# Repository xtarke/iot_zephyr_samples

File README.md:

# Zephyr RTOS Examples for Raspberry Pi Pico W

This repository contains a collection of IoT examples and utilities built with [Zephyr RTOS](https://zephyrproject.org/) specifically targeted for the Raspberry Pi Pico W. It provides starting points for Wi-Fi connectivity, basic GPIO manipulation, and debugging configurations.

## Repository Structure

| Sample / Folder | Description |
| :--- | :--- |
| **`blinky`** | The classic "Hello World" of embedded systems. Toggles the onboard LED to verify the basic build system and GPIO functionality. |
| **`_debugger`** | Documentation and configuration files for debugging the RP2040. Includes a comprehensive guide for using the **Black Magic Probe**. |
| **`wifi_scan`** | Demonstrates how to initialize the Wi-Fi interface and perform an active scan to discover nearby wireless networks. |
| **`wifi_shell`** | Integrates the Zephyr shell subsystem, allowing you to interactively manage and monitor Wi-Fi connections via a serial terminal. |
| **`wifi_static`** | A template for establishing a Wi-Fi connection using a hardcoded/static network configuration (SSID and password). |

---

## Prerequisites

Before building these examples, ensure you have the standard (tested with v4.4.0) Zephyr development environment set up:

1. **Zephyr SDK:** Installed and configured on your host machine.
2. **West Tool:** The Zephyr meta-tool installed via Python pip.
3. **Pico W Board:** A Raspberry Pi Pico W and a suitable micro-USB cable.

*For detailed setup instructions, refer to the [official Zephyr Getting Started Guide](https://docs.zephyrproject.org/latest/develop/getting_started/index.html).*

---

## Building and Flashing

To build any of the samples in this repository, navigate to the specific sample's directory or specify it in your `west build` command. 

### 1. Build the Sample
Use `west` to build the firmware for the Raspberry Pi Pico W. For example, to build the `blinky` sample:

```bash
west build -b rpi_pico/rp2040/w -p blinky

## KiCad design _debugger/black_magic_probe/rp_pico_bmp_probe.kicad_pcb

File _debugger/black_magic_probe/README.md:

# Black Magic Probe (BMP) Hardware Adapter

This documentation describes the hardware schematic for configuring an STM32 BlackPill as a Black Magic Probe (BMP) debugger. This design breaks out the essential debug and serial interfaces necessary for flashing and interacting with embedded targets.

## Schematic Overview

The schematic details the pin routing from the BlackPill's microcontroller to dedicated external connectors, providing a unified interface for hardware debugging.

### Exposed Debug & Serial Interfaces

The following critical signals are exposed for target interaction:
*   **Serial Wire Debug (SWD):** `SWDIO` and `SWCLK`.
*   **JTAG Interface:** `TDI` and `TDO`.
*   **UART Bridge:** `TX` and `RX` lines for target serial communication.
*   **Control & Power:** Target reset (`RST`), `+3.3V`, and `GND`.

### Hardware Connectors
The design organizes these signals into specific pin headers for modular target connections:
*   **J1:** Groups a 3-pin interface, likely designated for the UART bridge or basic target control.
*   **J2:** The primary 4-pin debug header, exposing the SWD/JTAG signaling lines.
*   **Auxiliary Connectors:** Multiple 2-pin connectors utilized for power delivery (`+3.3V`, `GND`) and other localized signal pairs.

### Status Indicators

The schematic includes visual indicators to monitor the probe's state during execution:
*   **D1 (Status LED):**  Pin `PC14`, typically used for general error or operational status indication
.
*   **D2 (UART LED):** Providesvisual feedback for serial bridge activity (TX/RX traffic).

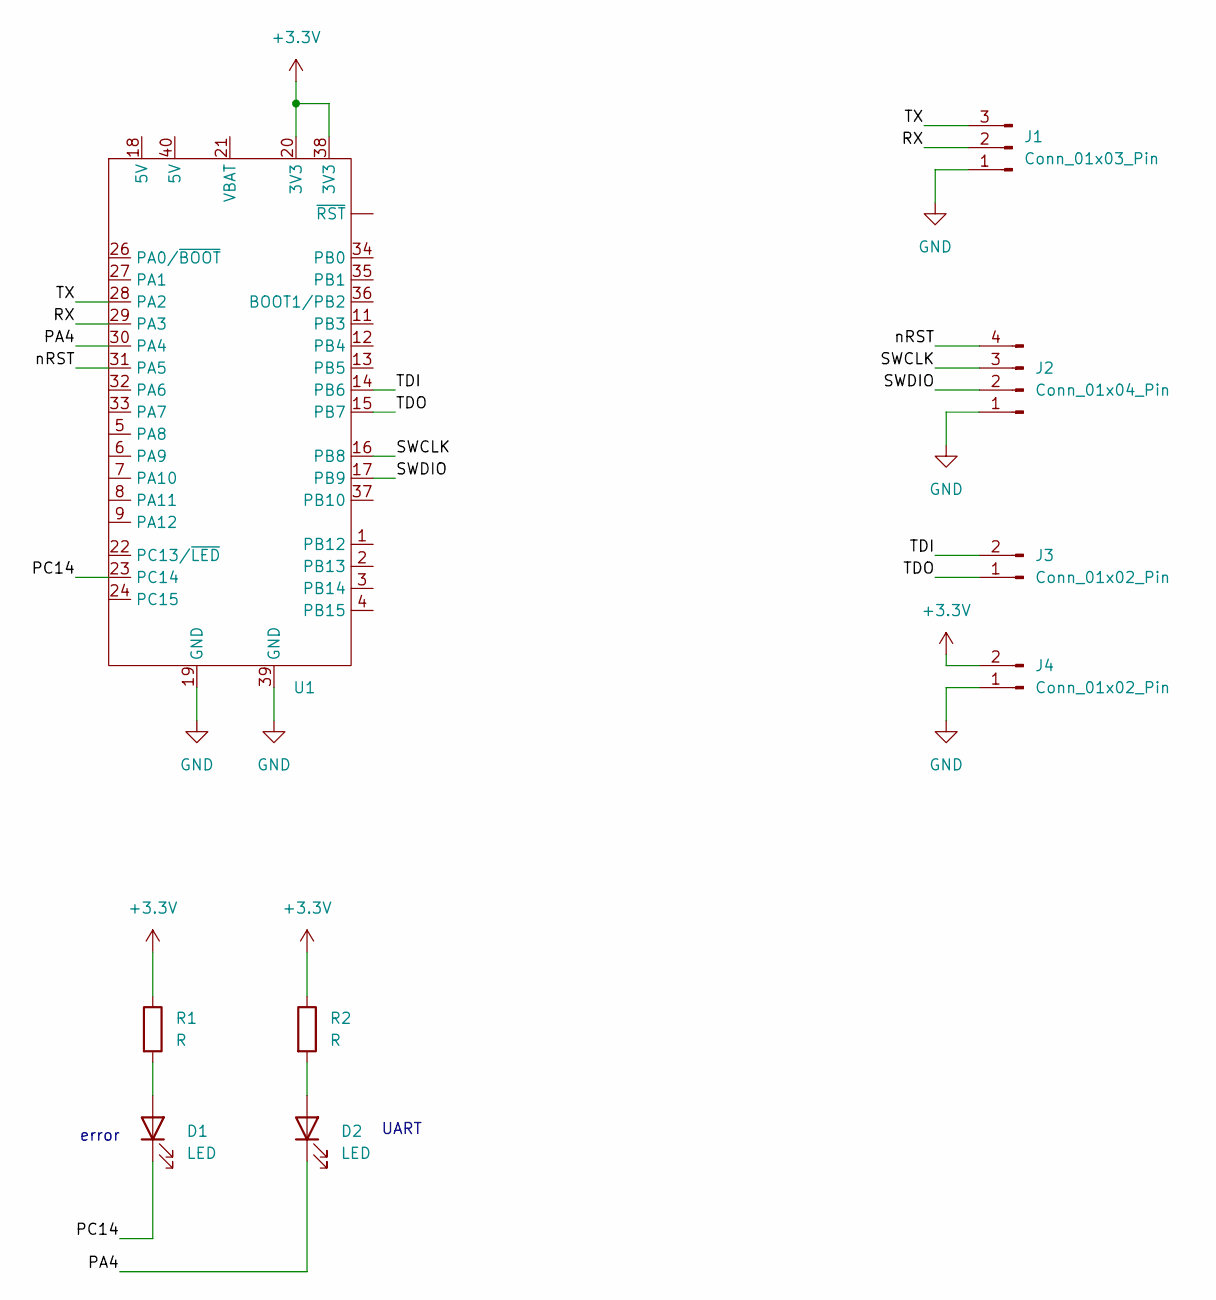
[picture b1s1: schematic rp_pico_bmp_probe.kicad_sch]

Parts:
D1, D2: LED; LED_D5.0mm
J1: Conn_01x03_Pin; Molex_KK-254_AE-6410-03A_1x03_P2.54mm_Vertical
J2: Conn_01x04_Pin; Molex_KK-254_AE-6410-04A_1x04_P2.54mm_Vertical
J3, J4: Conn_01x02_Pin; Molex_KK-254_AE-6410-02A_1x02_P2.54mm_Vertical
R1, R2: R; R_0805_2012Metric_Pad1.20x1.40mm_HandSolder
U1: Z_module_black_pill_STM32F411

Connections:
+3.3V: J4.2, R1.1, R2.1, U1.20 (3V3), U1.38 (3V3)
/PA4: D2.1 (K), U1.30 (PA4)
/PC14: D1.1 (K), U1.23 (PC14)
/RX: J1.2, U1.29 (PA3)
/SWCLK: J2.3, U1.16 (PB8)
/SWDIO: J2.2, U1.17 (PB9)
/TDI: J3.2, U1.14 (PB6)
/TDO: J3.1, U1.15 (PB7)
/TX: J1.3, U1.28 (PA2)
/nRST: J2.4, U1.31 (PA5)
GND: J1.1, J2.1, J4.1, U1.19 (GND), U1.39 (GND)
unnamed: D1.2 (A), R1.2
unnamed: D2.2 (A), R2.2

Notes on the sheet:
UART
error

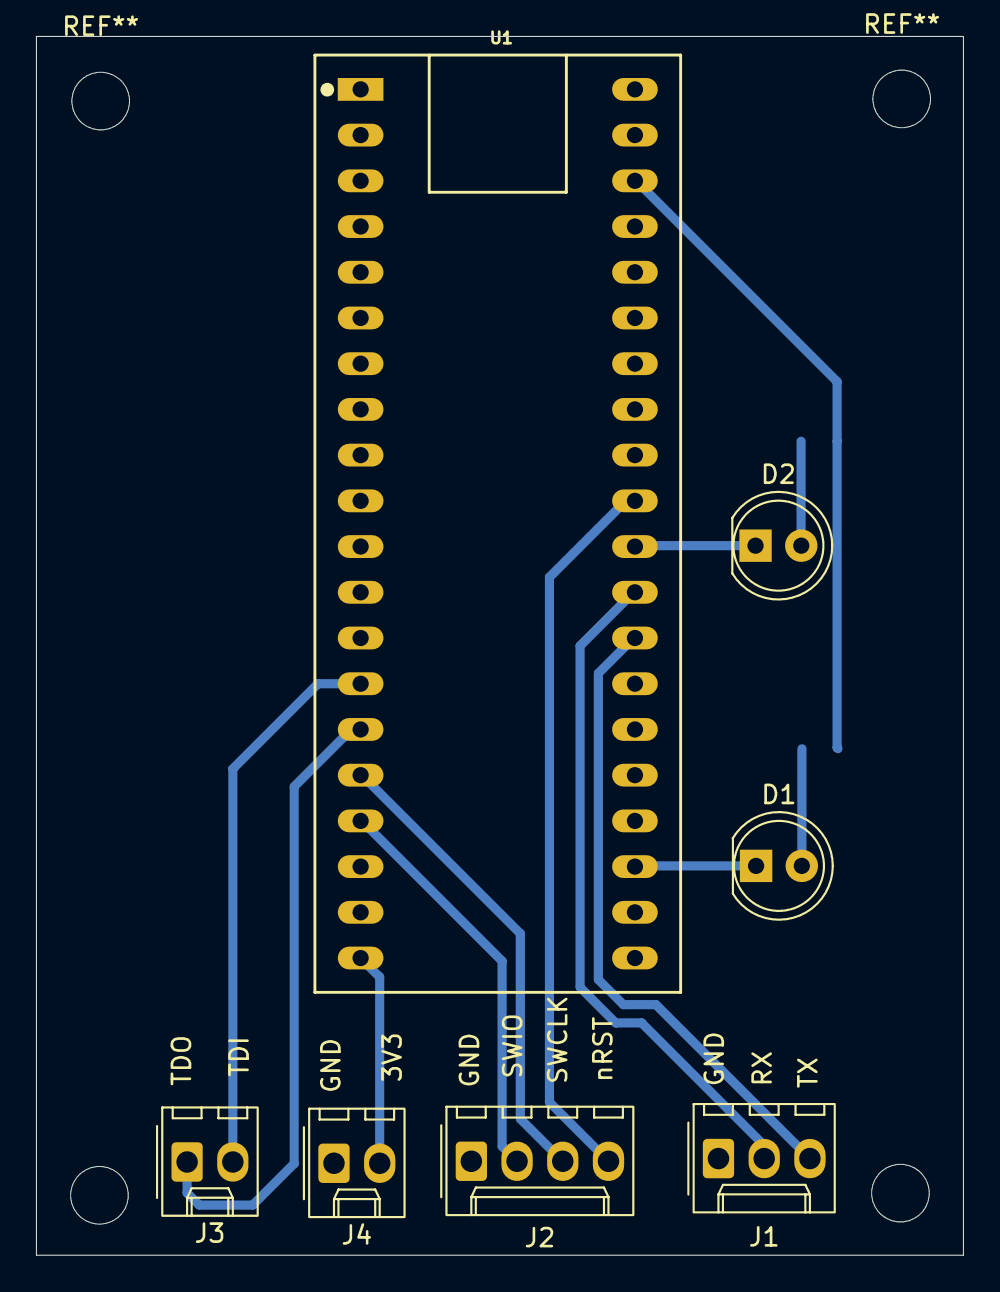
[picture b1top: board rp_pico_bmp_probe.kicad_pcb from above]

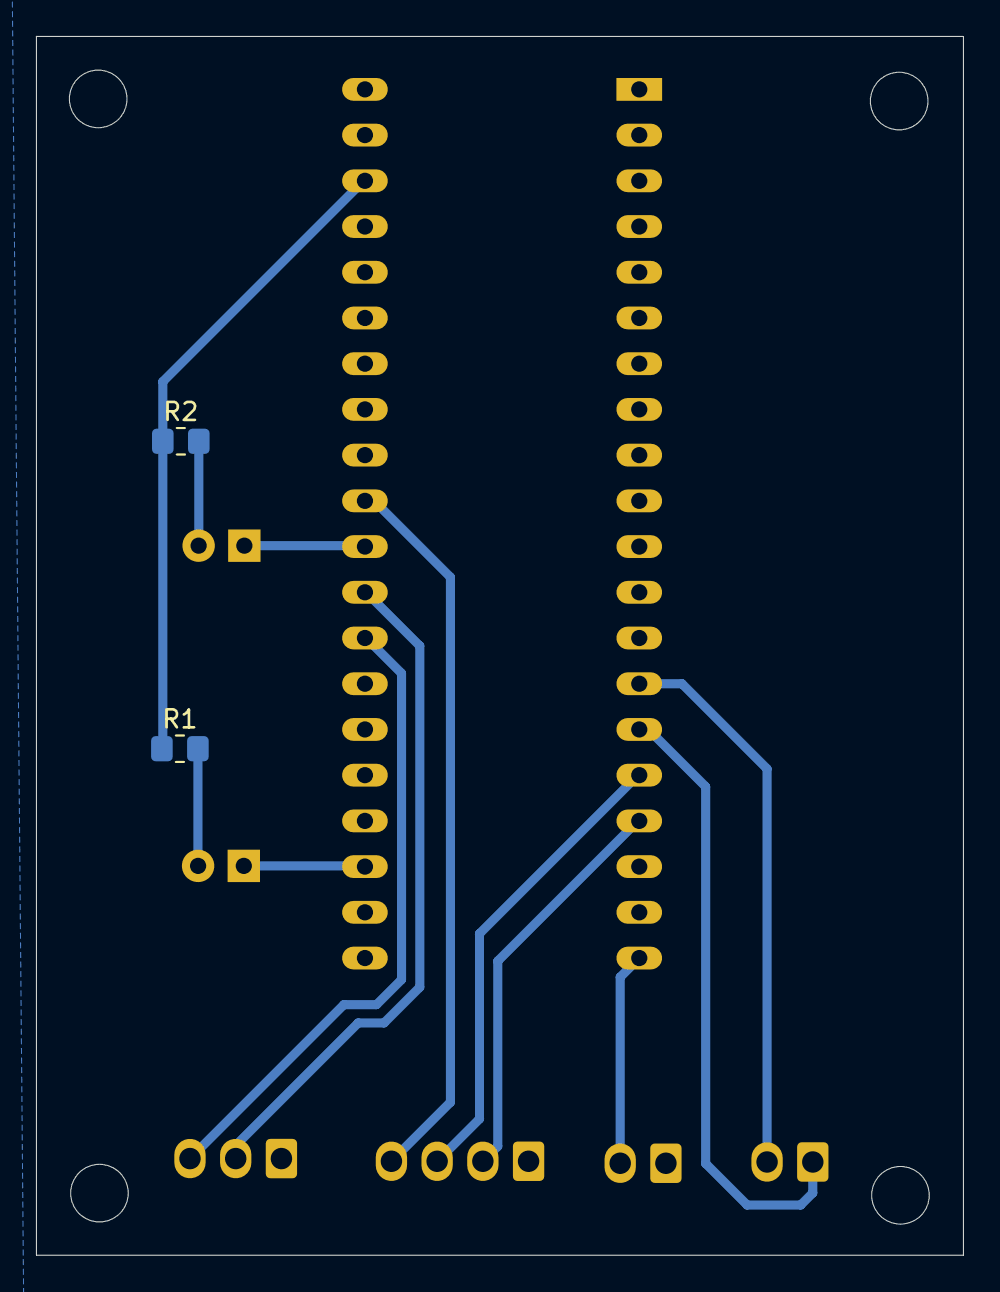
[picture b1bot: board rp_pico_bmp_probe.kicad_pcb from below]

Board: 2 copper layers, 51.5 x 67.7 mm, 9 parts (2 on the bottom side), 13 nets.
